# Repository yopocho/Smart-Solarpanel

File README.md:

# Smart Solarpanel Controller

This project contains the files for a device and housing that enables a solarpanel to control the MPPT of ten different sections of the same solarpanel to improve efficiency in partially-shaded conditions. This device is a self-contained version of a prototype S. Zahra Mirbagheri Golroodbari created for their PhD [dissertation](https://www.mdpi.com/1996-1073/11/1/250) on creating a better and more efficient solarpanel, in which she has succeded. 

On behalf of the Univerity of Utrecht, created at the Univeristy of Applied Sciences Utrecht.

## Electronics

### PCB

The PCB is designed in Kicad. It's rated to handle atleast 10A of current with an MPP output of 29,41V (221.75W).

To find the MPPT for each of the ten sections a dedicated LTM4611EV Buck-converter with INA226 and supporting components are used. They are controlled by a central STM32F103C8T6 microcontroller.

Programming the microcontroller is done through SWD via the provided 2.54mm pitch pins besides it.

### Firmware

The code for the microcontroller has at this moment not been written yet. The pinout and external crystal were determined by using CubeIDE as a tool to assist in layout, which can be used further to develop the firmware for the device.

## Mechanicals

The mechanical enclosure was calculated using Solidworks Simulation software to make sure it does not exceed the maximum allowed temperature of 70 degrees Celsius. For this reason the enclosure is made out of aluminium.

### Connections

The electrical connections are made using copper wire, as it is cheap and the resistance is low. Since a lot more of the cells are wired in parallel than in a conventional panel, thicker wire must be used to keep the losses under 2%. The wires are routed to the central PCB, where the MPP is calculated and everything is controlled.

The enclosure is waterproof with an IP65 rating. It is glued to the back of the panel. Several panels can be connected in series using standard connectors.

## Use

The provided files can be used as template to retrofit a classic solarpanel into a smart solarpanel. The PCB can be ordered and assembled, after which it can be fitted to the solar panel in the custom housing. 

## Built With

* [Kicad](https://www.kicad.org/) - EDA
* [STM32CubeIDE](https://www.st.com/en/development-tools/stm32cubeide.html) - IDE 
* [SolidWorks](https://www.solidworks.com/) - CAD

## Authors

* **Niels van der Zijden** - [Yopocho](https://github.com/yopocho)
* **Marnix Remmig** 
* **Teun Drijfhout** 
* **Silas Witmond** 

## License

This project is licensed under the MIT License

## Acknowledgments

* **Dr. Sara Mirbagheri Golroodbari** - Commisioner
* **Joost Kouijzer** - Group supervisor during this project
* **Marcel** - For letting our group use his lab during the project

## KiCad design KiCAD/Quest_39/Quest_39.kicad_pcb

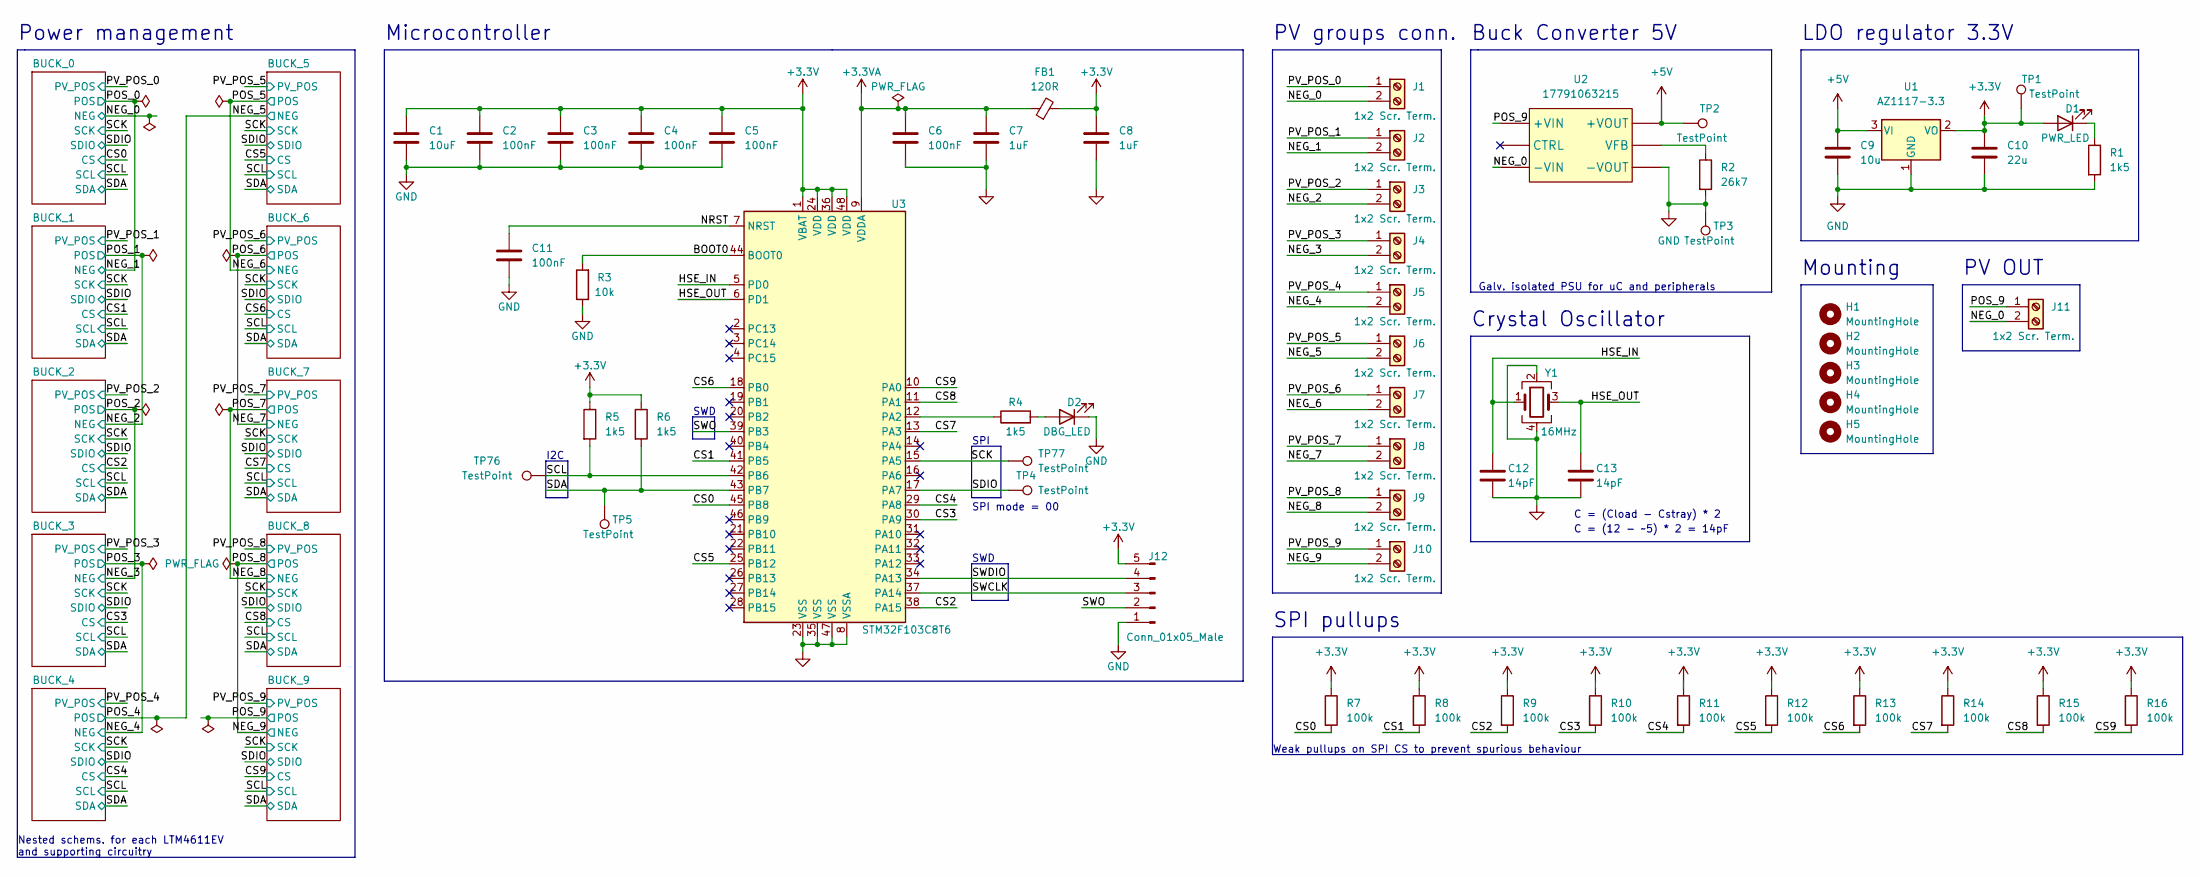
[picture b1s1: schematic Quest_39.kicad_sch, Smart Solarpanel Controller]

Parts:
C1: 10uF; C_0603_1608Metric
C2, C3, C4, C5, C6, C11: 100nF; C_0603_1608Metric
C7, C8: 1uF; C_0603_1608Metric
C9: 10u; C_0603_1608Metric
C10: 22u; C_0805_2012Metric
C12, C13: 14pF; C_0603_1608Metric
D1: PWR_LED; LED_1206_3216Metric
D2: DBG_LED; LED_1206_3216Metric
FB1: 120R; L_0603_1608Metric
H1, H2, H3, H4, H5: MountingHole; MountingHole_3mm
J1, J2, J3, J4, J5, J6, J7, J8, J9, J10, J11: 1x2 Scr. Term.; TB005-762-02BE
J12: Conn_01x05_Male; PinHeader_1x05_P2.54mm_Vertical
R1, R4, R5, R6: 1k5; R_1206_3216Metric
R2: 26k7; R_1206_3216Metric
R3: 10k; R_1206_3216Metric
R7, R8, R9, R10, R11, R12, R13, R14, R15, R16: 100k; R_1206_3216Metric
TP1, TP2, TP3, TP4, TP5, TP76, TP77: TestPoint; TestPoint_Pad_D2.0mm
U1: AZ1117-3.3; SOT-223-3_TabPin2
U2: 17791063215
U3: STM32F103C8T6; LQFP-48_7x7mm_P0.5mm
Y1: 16MHz; Crystal_SMD_3225-4Pin_3.2x2.5mm

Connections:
+3.3V: C1.1, C2.1, C3.1, C4.1, C5.1, C8.1, C10.1, D1.2 (A), FB1.2, J12.5, R5.1, R6.1, R7.1, R8.1, R9.1, R10.1, R11.1, R12.1, R13.1, R14.1, R15.1, R16.1, TP1.1, U1.2 (VO), U3.1 (VBAT), U3.24 (VDD), U3.36 (VDD), U3.48 (VDD)
+3.3VA: C6.1, C7.1, FB1.1, U3.9 (VDDA)
+5V: C9.1, TP2.1, U1.3 (VI), U2.6 (+VOUT); also elsewhere on the board
/BOOT0: R3.2, U3.44 (BOOT0)
/CS0: R7.2, U3.45 (PB8); also elsewhere on the board
/CS1: R8.2, U3.41 (PB5); also elsewhere on the board
/CS2: R9.2, U3.38 (PA15); also elsewhere on the board
/CS3: R10.2, U3.30 (PA9); also elsewhere on the board
/CS4: R11.2, U3.29 (PA8); also elsewhere on the board
/CS5: R12.2, U3.25 (PB12); also elsewhere on the board
/CS6: R13.2, U3.18 (PB0); also elsewhere on the board
/CS7: R14.2, U3.13 (PA3); also elsewhere on the board
/CS8: R15.2, U3.11 (PA1); also elsewhere on the board
/CS9: R16.2, U3.10 (PA0); also elsewhere on the board
/HSE_IN: C12.1, U3.5 (PD0), Y1.1
/HSE_OUT: C13.1, U3.6 (PD1), Y1.3
/NEG_0: J1.2, J11.2, U2.1 (-VIN); also elsewhere on the board
/NEG_1: J2.2; also elsewhere on the board
/NEG_2: J3.2; also elsewhere on the board
/NEG_3: J4.2; also elsewhere on the board
/NEG_4: J5.2; also elsewhere on the board
/NEG_5: J6.2; also elsewhere on the board
/NEG_6: J7.2; also elsewhere on the board
/NEG_7: J8.2; also elsewhere on the board
/NEG_8: J9.2; also elsewhere on the board
/NEG_9: J10.2; also elsewhere on the board
/NRST: C11.1, U3.7 (NRST)
/POS_9: J11.1, U2.2 (+VIN); also elsewhere on the board
/PV_POS_0: J1.1; also elsewhere on the board
/PV_POS_1: J2.1; also elsewhere on the board
/PV_POS_2: J3.1; also elsewhere on the board
/PV_POS_3: J4.1; also elsewhere on the board
/PV_POS_4: J5.1; also elsewhere on the board
/PV_POS_5: J6.1; also elsewhere on the board
/PV_POS_6: J7.1; also elsewhere on the board
/PV_POS_7: J8.1; also elsewhere on the board
/PV_POS_8: J9.1; also elsewhere on the board
/PV_POS_9: J10.1; also elsewhere on the board
/SCK: TP77.1, U3.15 (PA5); also elsewhere on the board
/SCL: R5.2, TP76.1, U3.42 (PB6); also elsewhere on the board
/SDA: R6.2, TP5.1, U3.43 (PB7); also elsewhere on the board
/SDIO: TP4.1, U3.17 (PA7); also elsewhere on the board
/SWCLK: J12.3, U3.37 (PA14)
/SWDIO: J12.4, U3.34 (PA13)
/SWO: J12.2, U3.39 (PB3)
GND: C1.2, C2.2, C3.2, C4.2, C5.2, C6.2, C7.2, C8.2, C9.2, C10.2, C11.2, C12.2, C13.2, D2.1 (K), J12.1, R1.2, R2.2, R3.1, TP3.1, U1.1 (GND), U2.7 (-VOUT), U3.8 (VSSA), U3.23 (VSS), U3.35 (VSS), U3.47 (VSS), Y1.2, Y1.4; also elsewhere on the board
unnamed: D1.1 (K), R1.1
unnamed: D2.2 (A), R4.2
unnamed: R2.1, U2.8 (VFB)
unnamed: R4.1, U3.12 (PA2)

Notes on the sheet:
Nested schems. for each LTM4611EV and supporting circuitry
SPI pullups
Buck Converter 5V
Crystal Oscillator
PV groups conn.
Power management
C = (12 - ~5) * 2 = 14pF
Microcontroller
SPI mode = 00
Galv. isolated PSU for uC and peripherals
C = (Cload - Cstray) * 2
Weak pullups on SPI CS to prevent spurious behaviour
I2C
Mounting
SWD
PV OUT
SWD
LDO regulator 3.3V
SPI

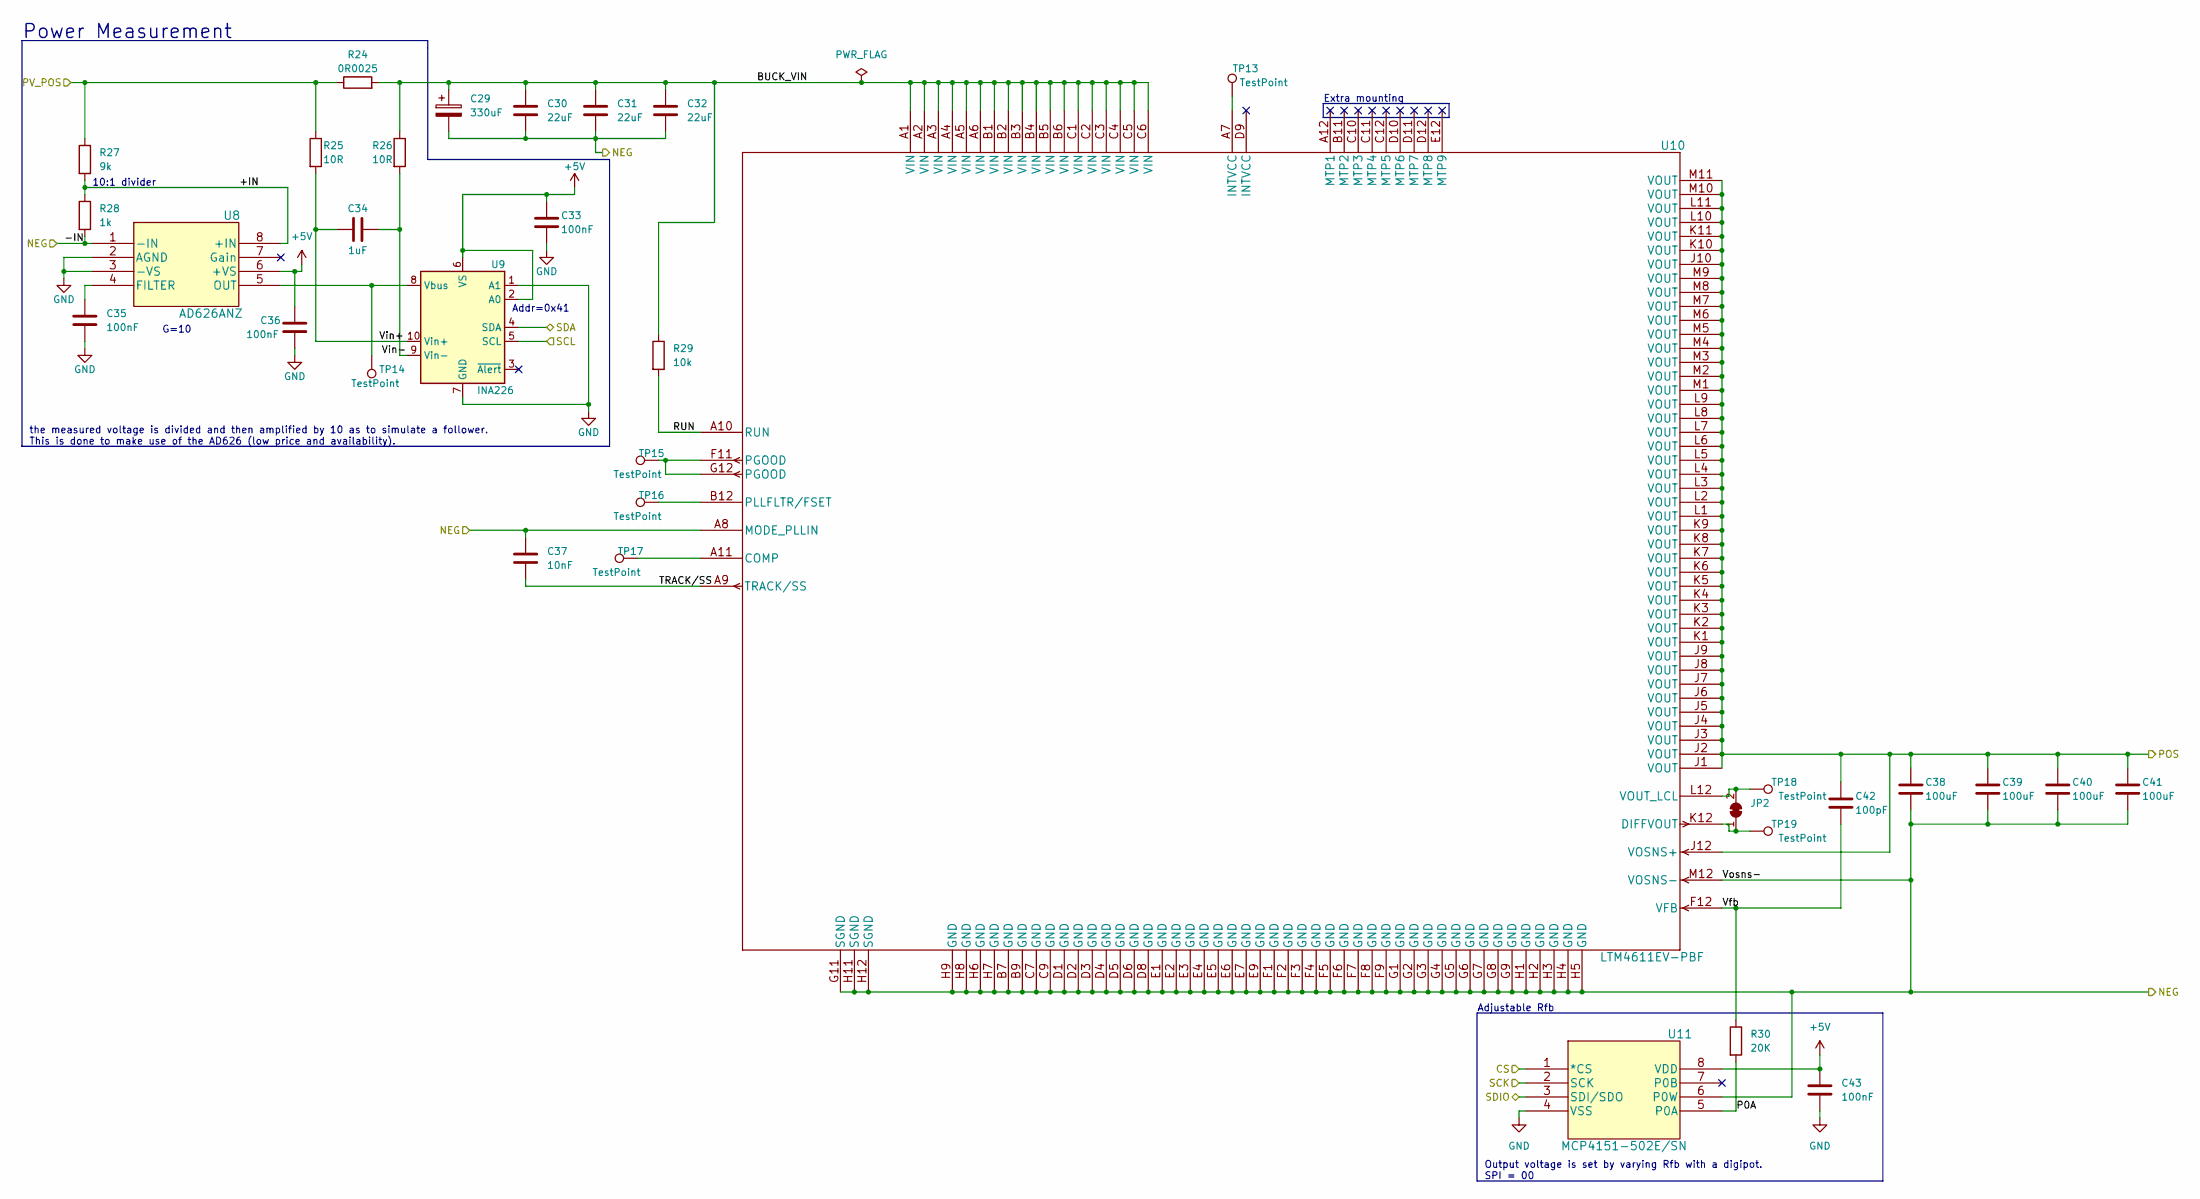
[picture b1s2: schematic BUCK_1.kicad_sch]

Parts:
C29: 330uF; CP_Elec_8x6.9
C30, C31, C32: 22uF; C_0805_2012Metric
C33, C35, C36, C43: 100nF; C_0603_1608Metric
C34: 1uF; C_0603_1608Metric
C37: 10nF; C_0603_1608Metric
C38, C39, C40, C41: 100uF; C_1206_3216Metric
C42: 100pF; C_0603_1608Metric
JP2: SolderJumper_2_Bridged; SolderJumper-2_P1.3mm_Bridged_RoundedPad1.0x1.5mm
R24: 0R0025; R_1206_3216Metric
R25, R26: 10R; R_0805_2012Metric
R27: 9k; R_0805_2012Metric
R28: 1k; R_0805_2012Metric
R29: 10k; R_0805_2012Metric
R30: 20K; R_0805_2012Metric
TP13, TP14, TP15, TP16, TP17, TP18, TP19: TestPoint; TestPoint_Pad_D2.0mm
U8: AD626ANZ; DIP-8_W7.62mm_Socket_LongPads
U9: INA226; VSSOP-10_3x3mm_P0.5mm
U10: LTM4611EV-PBF; Linear_LGA-133_15.0x15.0mm_Layout12x12_P1.27mm
U11: MCP4151-502E/SN; MSOP-8_3x3mm_P0.65mm

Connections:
+5V: C33.1, C36.1, C43.1, U8.6 (+VS), U9.2 (A0), U9.6 (VS), U11.8 (VDD); also elsewhere on the board
/BUCK_1/+IN: R27.2, R28.1, U8.8 (+IN)
/BUCK_1/BUCK_VIN: C29.1, C30.1, C31.1, C32.1, R24.2, R26.1, R29.1, U10.A1 (VIN), U10.A2 (VIN), U10.A3 (VIN), U10.A4 (VIN), U10.A5 (VIN), U10.A6 (VIN), U10.B1 (VIN), U10.B2 (VIN), U10.B3 (VIN), U10.B4 (VIN), U10.B5 (VIN), U10.B6 (VIN), U10.C1 (VIN), U10.C2 (VIN), U10.C3 (VIN), U10.C4 (VIN), U10.C5 (VIN), U10.C6 (VIN)
/BUCK_1/P0A: R30.2, U11.5 (P0A)
/BUCK_1/RUN: R29.2, U10.A10 (RUN)
/BUCK_1/TRACK/SS: C37.2, U10.A9 (TRACK/SS)
/BUCK_1/Vfb: C42.2, R30.1, U10.F12 (VFB)
/BUCK_1/Vin+: C34.1, R25.2, U9.10 (Vin+)
/BUCK_1/Vin-: C34.2, R26.2, U9.9 (Vin-)
/CS1: U11.1 (*CS); also elsewhere on the board
/NEG_1: C29.2, C30.2, C31.2, C32.2, C37.1, C38.2, C39.2, C40.2, C41.2, R28.2, U8.1 (-IN), U10.A8 (MODE_PLLIN), U10.B7 (GND), U10.B9 (GND), U10.C7 (GND), U10.C9 (GND), U10.D1 (GND), U10.D2 (GND), U10.D3 (GND), U10.D4 (GND), U10.D5 (GND), U10.D6 (GND), U10.D8 (GND), U10.E1 (GND), U10.E2 (GND), U10.E3 (GND), U10.E4 (GND), U10.E5 (GND), U10.E6 (GND), U10.E7 (GND), U10.E9 (GND), U10.F1 (GND), U10.F2 (GND), U10.F3 (GND), U10.F4 (GND), U10.F5 (GND), U10.F6 (GND), U10.F7 (GND), U10.F8 (GND), U10.F9 (GND), U10.G1 (GND), U10.G2 (GND), U10.G3 (GND), U10.G4 (GND), U10.G5 (GND), U10.G6 (GND), U10.G7 (GND), U10.G8 (GND), U10.G9 (GND), U10.G11 (SGND), U10.H1 (GND), U10.H2 (GND), U10.H3 (GND), U10.H4 (GND), U10.H5 (GND), U10.H6 (GND), U10.H7 (GND), U10.H8 (GND), U10.H9 (GND), U10.H11 (SGND), U10.H12 (SGND), U10.M12 (VOSNS-), U11.6 (P0W); also elsewhere on the board
/NEG_2: C38.1, C39.1, C40.1, C41.1, C42.1, U10.J1 (VOUT), U10.J2 (VOUT), U10.J3 (VOUT), U10.J4 (VOUT), U10.J5 (VOUT), U10.J6 (VOUT), U10.J7 (VOUT), U10.J8 (VOUT), U10.J9 (VOUT), U10.J10 (VOUT), U10.J12 (VOSNS+), U10.K1 (VOUT), U10.K2 (VOUT), U10.K3 (VOUT), U10.K4 (VOUT), U10.K5 (VOUT), U10.K6 (VOUT), U10.K7 (VOUT), U10.K8 (VOUT), U10.K9 (VOUT), U10.K10 (VOUT), U10.K11 (VOUT), U10.L1 (VOUT), U10.L2 (VOUT), U10.L3 (VOUT), U10.L4 (VOUT), U10.L5 (VOUT), U10.L6 (VOUT), U10.L7 (VOUT), U10.L8 (VOUT), U10.L9 (VOUT), U10.L10 (VOUT), U10.L11 (VOUT), U10.M1 (VOUT), U10.M2 (VOUT), U10.M3 (VOUT), U10.M4 (VOUT), U10.M5 (VOUT), U10.M6 (VOUT), U10.M7 (VOUT), U10.M8 (VOUT), U10.M9 (VOUT), U10.M10 (VOUT), U10.M11 (VOUT); also elsewhere on the board
/PV_POS_1: R24.1, R25.1, R27.1; also elsewhere on the board
/SCK: U11.2 (SCK); also elsewhere on the board
/SCL: U9.5 (SCL); also elsewhere on the board
/SDA: U9.4 (SDA); also elsewhere on the board
/SDIO: U11.3 (SDI/SDO); also elsewhere on the board
GND: C33.2, C35.2, C36.2, C43.2, U8.2 (AGND), U8.3 (-VS), U9.1 (A1), U9.7 (GND), U11.4 (VSS); also elsewhere on the board
unnamed: C35.1, U8.4 (FILTER)
unnamed: JP2.1 (A), TP19.1, U10.K12 (DIFFVOUT)
unnamed: JP2.2 (B), TP18.1, U10.L12 (VOUT_LCL)
unnamed: TP13.1, U10.A7 (INTVCC)
unnamed: TP14.1, U8.5 (OUT), U9.8 (Vbus)
unnamed: TP15.1, U10.F11 (PGOOD), U10.G12 (PGOOD)
unnamed: TP16.1, U10.B12 (PLLFLTR/FSET)
unnamed: TP17.1, U10.A11 (COMP)

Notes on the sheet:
G=10
Extra mounting
Power Measurement
10:1 divider
Adjustable Rfb
Output voltage is set by varying Rfb with a digipot. SPI = 00
Addr=0x41
the measured voltage is divided and then amplified by 10 as to simulate a follower. This is done to make use of the AD626 (low price and availability).

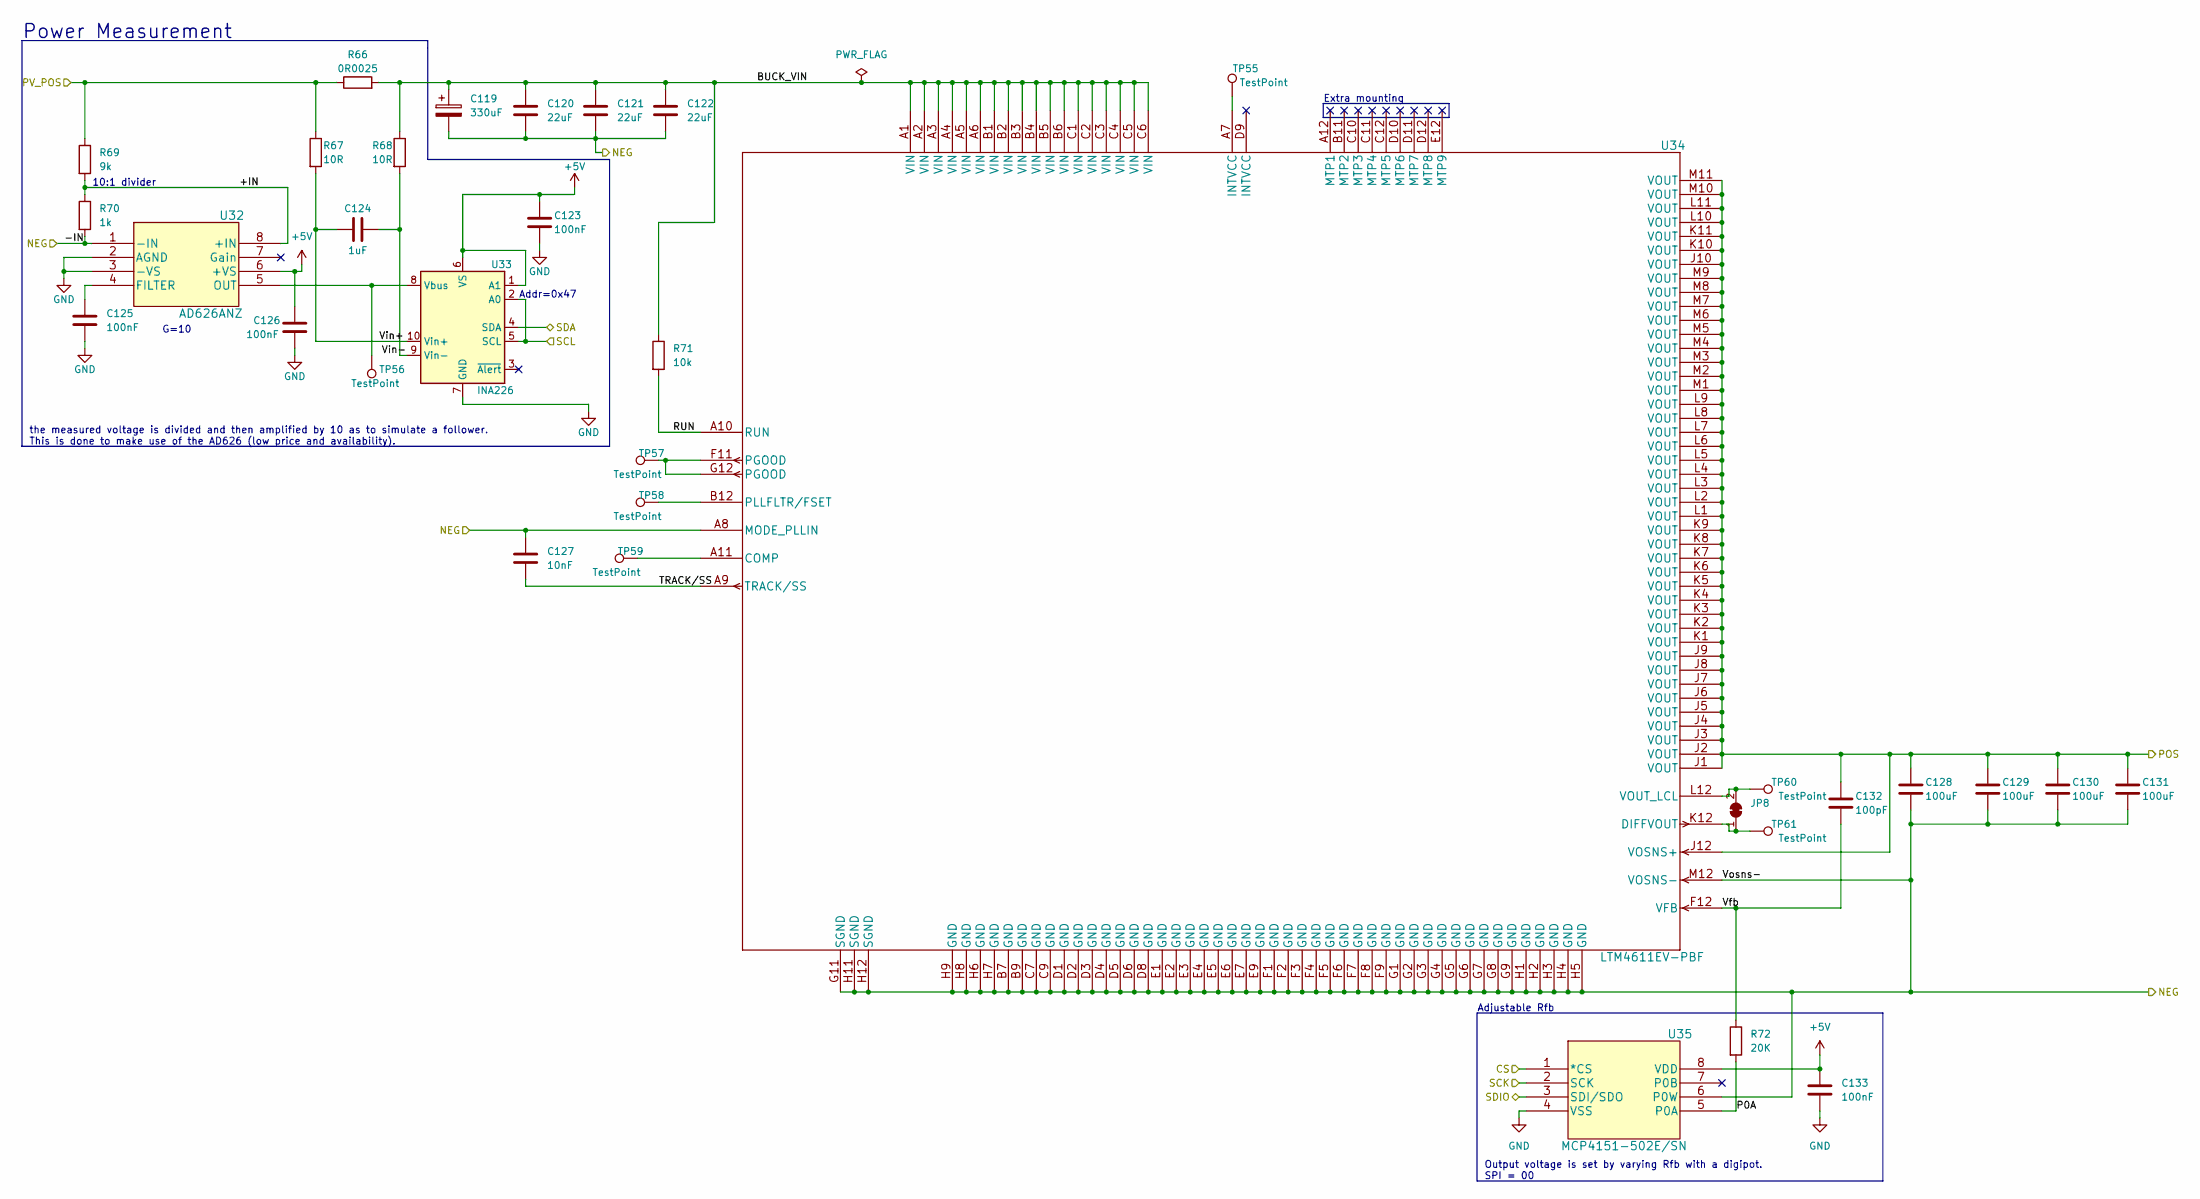
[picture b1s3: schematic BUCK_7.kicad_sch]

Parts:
C119: 330uF; CP_Elec_8x6.9
C120, C121, C122: 22uF; C_0805_2012Metric
C123, C125, C126, C133: 100nF; C_0603_1608Metric
C124: 1uF; C_0603_1608Metric
C127: 10nF; C_0603_1608Metric
C128, C129, C130, C131: 100uF; C_1206_3216Metric
C132: 100pF; C_0603_1608Metric
JP8: SolderJumper_2_Bridged; SolderJumper-2_P1.3mm_Bridged_RoundedPad1.0x1.5mm
R66: 0R0025; R_1206_3216Metric
R67, R68: 10R; R_0805_2012Metric
R69: 9k; R_0805_2012Metric
R70: 1k; R_0805_2012Metric
R71: 10k; R_0805_2012Metric
R72: 20K; R_0805_2012Metric
TP55, TP56, TP57, TP58, TP59, TP60, TP61: TestPoint; TestPoint_Pad_D2.0mm
U32: AD626ANZ; DIP-8_W7.62mm_Socket_LongPads
U33: INA226; VSSOP-10_3x3mm_P0.5mm
U34: LTM4611EV-PBF; Linear_LGA-133_15.0x15.0mm_Layout12x12_P1.27mm
U35: MCP4151-502E/SN; MSOP-8_3x3mm_P0.65mm

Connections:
+5V: C123.1, C126.1, C133.1, U32.6 (+VS), U33.1 (A1), U33.6 (VS), U35.8 (VDD); also elsewhere on the board
/BUCK_7/+IN: R69.2, R70.1, U32.8 (+IN)
/BUCK_7/BUCK_VIN: C119.1, C120.1, C121.1, C122.1, R66.2, R68.1, R71.1, U34.A1 (VIN), U34.A2 (VIN), U34.A3 (VIN), U34.A4 (VIN), U34.A5 (VIN), U34.A6 (VIN), U34.B1 (VIN), U34.B2 (VIN), U34.B3 (VIN), U34.B4 (VIN), U34.B5 (VIN), U34.B6 (VIN), U34.C1 (VIN), U34.C2 (VIN), U34.C3 (VIN), U34.C4 (VIN), U34.C5 (VIN), U34.C6 (VIN)
/BUCK_7/P0A: R72.2, U35.5 (P0A)
/BUCK_7/RUN: R71.2, U34.A10 (RUN)
/BUCK_7/TRACK/SS: C127.2, U34.A9 (TRACK/SS)
/BUCK_7/Vfb: C132.2, R72.1, U34.F12 (VFB)
/BUCK_7/Vin+: C124.1, R67.2, U33.10 (Vin+)
/BUCK_7/Vin-: C124.2, R68.2, U33.9 (Vin-)
/CS7: U35.1 (*CS); also elsewhere on the board
/NEG_7: C119.2, C120.2, C121.2, C122.2, C127.1, C128.2, C129.2, C130.2, C131.2, R70.2, U32.1 (-IN), U34.A8 (MODE_PLLIN), U34.B7 (GND), U34.B9 (GND), U34.C7 (GND), U34.C9 (GND), U34.D1 (GND), U34.D2 (GND), U34.D3 (GND), U34.D4 (GND), U34.D5 (GND), U34.D6 (GND), U34.D8 (GND), U34.E1 (GND), U34.E2 (GND), U34.E3 (GND), U34.E4 (GND), U34.E5 (GND), U34.E6 (GND), U34.E7 (GND), U34.E9 (GND), U34.F1 (GND), U34.F2 (GND), U34.F3 (GND), U34.F4 (GND), U34.F5 (GND), U34.F6 (GND), U34.F7 (GND), U34.F8 (GND), U34.F9 (GND), U34.G1 (GND), U34.G2 (GND), U34.G3 (GND), U34.G4 (GND), U34.G5 (GND), U34.G6 (GND), U34.G7 (GND), U34.G8 (GND), U34.G9 (GND), U34.G11 (SGND), U34.H1 (GND), U34.H2 (GND), U34.H3 (GND), U34.H4 (GND), U34.H5 (GND), U34.H6 (GND), U34.H7 (GND), U34.H8 (GND), U34.H9 (GND), U34.H11 (SGND), U34.H12 (SGND), U34.M12 (VOSNS-), U35.6 (P0W); also elsewhere on the board
/NEG_8: C128.1, C129.1, C130.1, C131.1, C132.1, U34.J1 (VOUT), U34.J2 (VOUT), U34.J3 (VOUT), U34.J4 (VOUT), U34.J5 (VOUT), U34.J6 (VOUT), U34.J7 (VOUT), U34.J8 (VOUT), U34.J9 (VOUT), U34.J10 (VOUT), U34.J12 (VOSNS+), U34.K1 (VOUT), U34.K2 (VOUT), U34.K3 (VOUT), U34.K4 (VOUT), U34.K5 (VOUT), U34.K6 (VOUT), U34.K7 (VOUT), U34.K8 (VOUT), U34.K9 (VOUT), U34.K10 (VOUT), U34.K11 (VOUT), U34.L1 (VOUT), U34.L2 (VOUT), U34.L3 (VOUT), U34.L4 (VOUT), U34.L5 (VOUT), U34.L6 (VOUT), U34.L7 (VOUT), U34.L8 (VOUT), U34.L9 (VOUT), U34.L10 (VOUT), U34.L11 (VOUT), U34.M1 (VOUT), U34.M2 (VOUT), U34.M3 (VOUT), U34.M4 (VOUT), U34.M5 (VOUT), U34.M6 (VOUT), U34.M7 (VOUT), U34.M8 (VOUT), U34.M9 (VOUT), U34.M10 (VOUT), U34.M11 (VOUT); also elsewhere on the board
/PV_POS_7: R66.1, R67.1, R69.1; also elsewhere on the board
/SCK: U35.2 (SCK); also elsewhere on the board
/SCL: U33.2 (A0), U33.5 (SCL); also elsewhere on the board
/SDA: U33.4 (SDA); also elsewhere on the board
/SDIO: U35.3 (SDI/SDO); also elsewhere on the board
GND: C123.2, C125.2, C126.2, C133.2, U32.2 (AGND), U32.3 (-VS), U33.7 (GND), U35.4 (VSS); also elsewhere on the board
unnamed: C125.1, U32.4 (FILTER)
unnamed: JP8.1 (A), TP61.1, U34.K12 (DIFFVOUT)
unnamed: JP8.2 (B), TP60.1, U34.L12 (VOUT_LCL)
unnamed: TP55.1, U34.A7 (INTVCC)
unnamed: TP56.1, U32.5 (OUT), U33.8 (Vbus)
unnamed: TP57.1, U34.F11 (PGOOD), U34.G12 (PGOOD)
unnamed: TP58.1, U34.B12 (PLLFLTR/FSET)
unnamed: TP59.1, U34.A11 (COMP)

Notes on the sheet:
Output voltage is set by varying Rfb with a digipot. SPI = 00
the measured voltage is divided and then amplified by 10 as to simulate a follower. This is done to make use of the AD626 (low price and availability).
Extra mounting
Adjustable Rfb
G=10
Addr=0x47
10:1 divider
Power Measurement

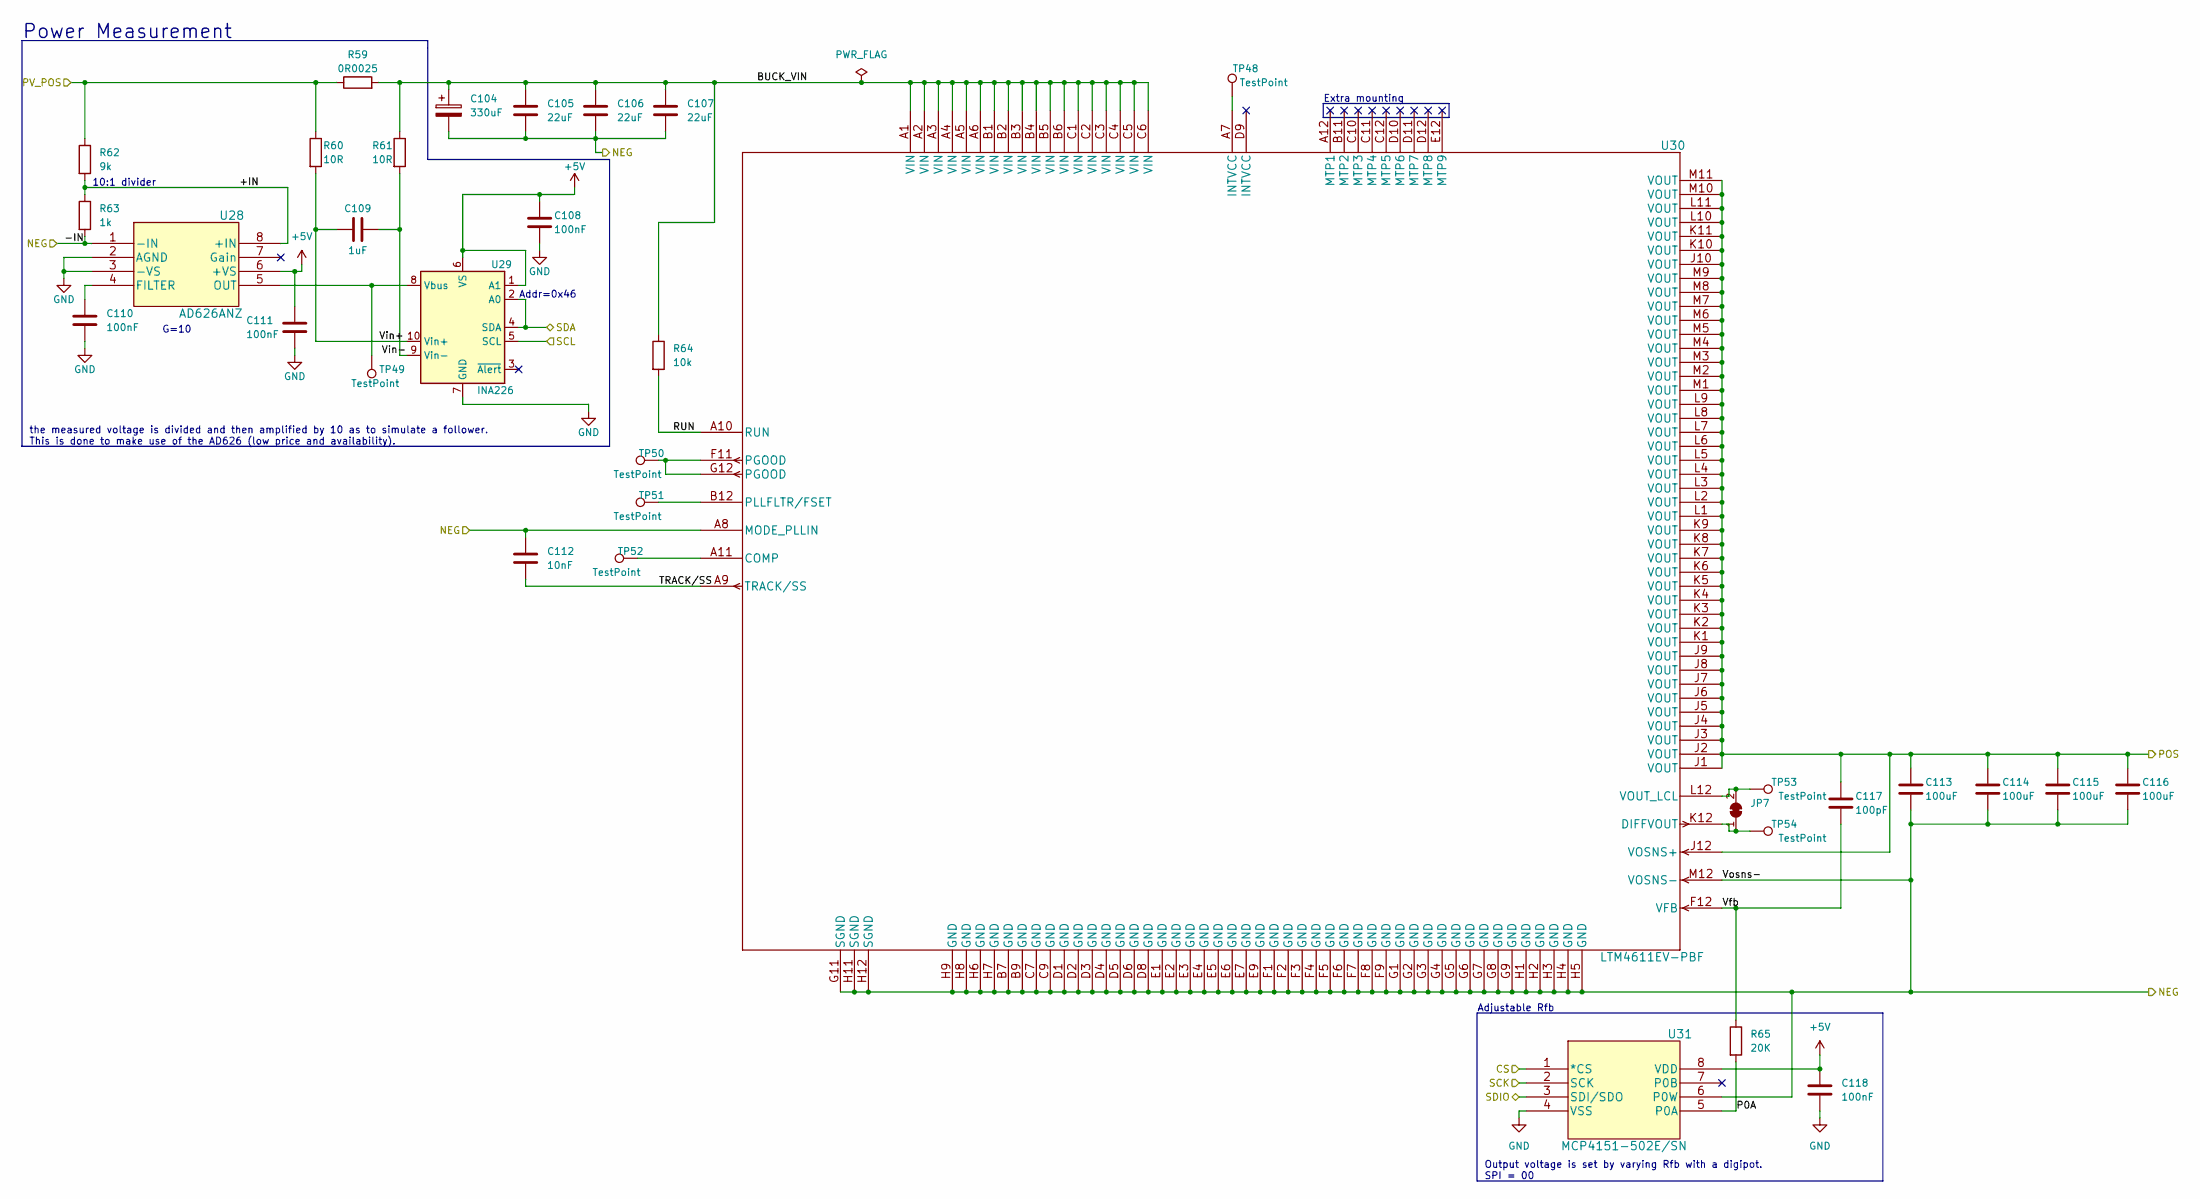
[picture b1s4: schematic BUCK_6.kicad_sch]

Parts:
C104: 330uF; CP_Elec_8x6.9
C105, C106, C107: 22uF; C_0805_2012Metric
C108, C110, C111, C118: 100nF; C_0603_1608Metric
C109: 1uF; C_0603_1608Metric
C112: 10nF; C_0603_1608Metric
C113, C114, C115, C116: 100uF; C_1206_3216Metric
C117: 100pF; C_0603_1608Metric
JP7: SolderJumper_2_Bridged; SolderJumper-2_P1.3mm_Bridged_RoundedPad1.0x1.5mm
R59: 0R0025; R_1206_3216Metric
R60, R61: 10R; R_0805_2012Metric
R62: 9k; R_0805_2012Metric
R63: 1k; R_0805_2012Metric
R64: 10k; R_0805_2012Metric
R65: 20K; R_0805_2012Metric
TP48, TP49, TP50, TP51, TP52, TP53, TP54: TestPoint; TestPoint_Pad_D2.0mm
U28: AD626ANZ; DIP-8_W7.62mm_Socket_LongPads
U29: INA226; VSSOP-10_3x3mm_P0.5mm
U30: LTM4611EV-PBF; Linear_LGA-133_15.0x15.0mm_Layout12x12_P1.27mm
U31: MCP4151-502E/SN; MSOP-8_3x3mm_P0.65mm

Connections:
+5V: C108.1, C111.1, C118.1, U28.6 (+VS), U29.1 (A1), U29.6 (VS), U31.8 (VDD); also elsewhere on the board
/BUCK_6/+IN: R62.2, R63.1, U28.8 (+IN)
/BUCK_6/BUCK_VIN: C104.1, C105.1, C106.1, C107.1, R59.2, R61.1, R64.1, U30.A1 (VIN), U30.A2 (VIN), U30.A3 (VIN), U30.A4 (VIN), U30.A5 (VIN), U30.A6 (VIN), U30.B1 (VIN), U30.B2 (VIN), U30.B3 (VIN), U30.B4 (VIN), U30.B5 (VIN), U30.B6 (VIN), U30.C1 (VIN), U30.C2 (VIN), U30.C3 (VIN), U30.C4 (VIN), U30.C5 (VIN), U30.C6 (VIN)
/BUCK_6/P0A: R65.2, U31.5 (P0A)
/BUCK_6/RUN: R64.2, U30.A10 (RUN)
/BUCK_6/TRACK/SS: C112.2, U30.A9 (TRACK/SS)
/BUCK_6/Vfb: C117.2, R65.1, U30.F12 (VFB)
/BUCK_6/Vin+: C109.1, R60.2, U29.10 (Vin+)
/BUCK_6/Vin-: C109.2, R61.2, U29.9 (Vin-)
/CS6: U31.1 (*CS); also elsewhere on the board
/NEG_6: C104.2, C105.2, C106.2, C107.2, C112.1, C113.2, C114.2, C115.2, C116.2, R63.2, U28.1 (-IN), U30.A8 (MODE_PLLIN), U30.B7 (GND), U30.B9 (GND), U30.C7 (GND), U30.C9 (GND), U30.D1 (GND), U30.D2 (GND), U30.D3 (GND), U30.D4 (GND), U30.D5 (GND), U30.D6 (GND), U30.D8 (GND), U30.E1 (GND), U30.E2 (GND), U30.E3 (GND), U30.E4 (GND), U30.E5 (GND), U30.E6 (GND), U30.E7 (GND), U30.E9 (GND), U30.F1 (GND), U30.F2 (GND), U30.F3 (GND), U30.F4 (GND), U30.F5 (GND), U30.F6 (GND), U30.F7 (GND), U30.F8 (GND), U30.F9 (GND), U30.G1 (GND), U30.G2 (GND), U30.G3 (GND), U30.G4 (GND), U30.G5 (GND), U30.G6 (GND), U30.G7 (GND), U30.G8 (GND), U30.G9 (GND), U30.G11 (SGND), U30.H1 (GND), U30.H2 (GND), U30.H3 (GND), U30.H4 (GND), U30.H5 (GND), U30.H6 (GND), U30.H7 (GND), U30.H8 (GND), U30.H9 (GND), U30.H11 (SGND), U30.H12 (SGND), U30.M12 (VOSNS-), U31.6 (P0W); also elsewhere on the board
/NEG_7: C113.1, C114.1, C115.1, C116.1, C117.1, U30.J1 (VOUT), U30.J2 (VOUT), U30.J3 (VOUT), U30.J4 (VOUT), U30.J5 (VOUT), U30.J6 (VOUT), U30.J7 (VOUT), U30.J8 (VOUT), U30.J9 (VOUT), U30.J10 (VOUT), U30.J12 (VOSNS+), U30.K1 (VOUT), U30.K2 (VOUT), U30.K3 (VOUT), U30.K4 (VOUT), U30.K5 (VOUT), U30.K6 (VOUT), U30.K7 (VOUT), U30.K8 (VOUT), U30.K9 (VOUT), U30.K10 (VOUT), U30.K11 (VOUT), U30.L1 (VOUT), U30.L2 (VOUT), U30.L3 (VOUT), U30.L4 (VOUT), U30.L5 (VOUT), U30.L6 (VOUT), U30.L7 (VOUT), U30.L8 (VOUT), U30.L9 (VOUT), U30.L10 (VOUT), U30.L11 (VOUT), U30.M1 (VOUT), U30.M2 (VOUT), U30.M3 (VOUT), U30.M4 (VOUT), U30.M5 (VOUT), U30.M6 (VOUT), U30.M7 (VOUT), U30.M8 (VOUT), U30.M9 (VOUT), U30.M10 (VOUT), U30.M11 (VOUT); also elsewhere on the board
/PV_POS_6: R59.1, R60.1, R62.1; also elsewhere on the board
/SCK: U31.2 (SCK); also elsewhere on the board
/SCL: U29.5 (SCL); also elsewhere on the board
/SDA: U29.2 (A0), U29.4 (SDA); also elsewhere on the board
/SDIO: U31.3 (SDI/SDO); also elsewhere on the board
GND: C108.2, C110.2, C111.2, C118.2, U28.2 (AGND), U28.3 (-VS), U29.7 (GND), U31.4 (VSS); also elsewhere on the board
unnamed: C110.1, U28.4 (FILTER)
unnamed: JP7.1 (A), TP54.1, U30.K12 (DIFFVOUT)
unnamed: JP7.2 (B), TP53.1, U30.L12 (VOUT_LCL)
unnamed: TP48.1, U30.A7 (INTVCC)
unnamed: TP49.1, U28.5 (OUT), U29.8 (Vbus)
unnamed: TP50.1, U30.F11 (PGOOD), U30.G12 (PGOOD)
unnamed: TP51.1, U30.B12 (PLLFLTR/FSET)
unnamed: TP52.1, U30.A11 (COMP)

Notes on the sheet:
Extra mounting
Addr=0x46
10:1 divider
the measured voltage is divided and then amplified by 10 as to simulate a follower. This is done to make use of the AD626 (low price and availability).
Power Measurement
Output voltage is set by varying Rfb with a digipot. SPI = 00
Adjustable Rfb
G=10
